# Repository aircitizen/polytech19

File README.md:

# polytech19

## Architecture
Le projet se décompose en trois parties
- Code du noeud LoRaWan
- PCB du noeud LoRaWan
- PCB de la gateway LoRaWan

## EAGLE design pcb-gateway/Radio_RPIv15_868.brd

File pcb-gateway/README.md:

# PCB gateway

Ici se situent les fichiers EAGLE du PCB de la gateway qui se connecte sur une Raspberry Pi B 3+.
Il y a également la BOM et des images.

Travail réalisé à partir du projet [https://github.com/will127534/LoRa-concentrator](https://github.com/will127534/LoRa-concentrator)

## RPi IO Mapping

| Function    | RPi Pin  | RPi IO Names                     |
| ----------- | -------- | -------------------------------- |
| SPI MOSI    | 19       | SPI-MOSI, GPIO10                 |
| SPI MISO    | 21       | SPI-MISO, GPIO9                  |
| SPI SCK     | 23       | SPI-SCLK, GPIO11                 |
| SPI CSN     | 24 OR 26 | SPI-CS0, GPIO8 OR SPI-CS1, GPIO7 |
| Reset       | 22       | GPIO25                           |
| GPS UART TX | 10       | UART0-RX, GPIO15                 |
| GPS UART RX | 8        | UART0-TX, GPIO14                 |
| GPS PPS     | 29       | GPIO5                            |

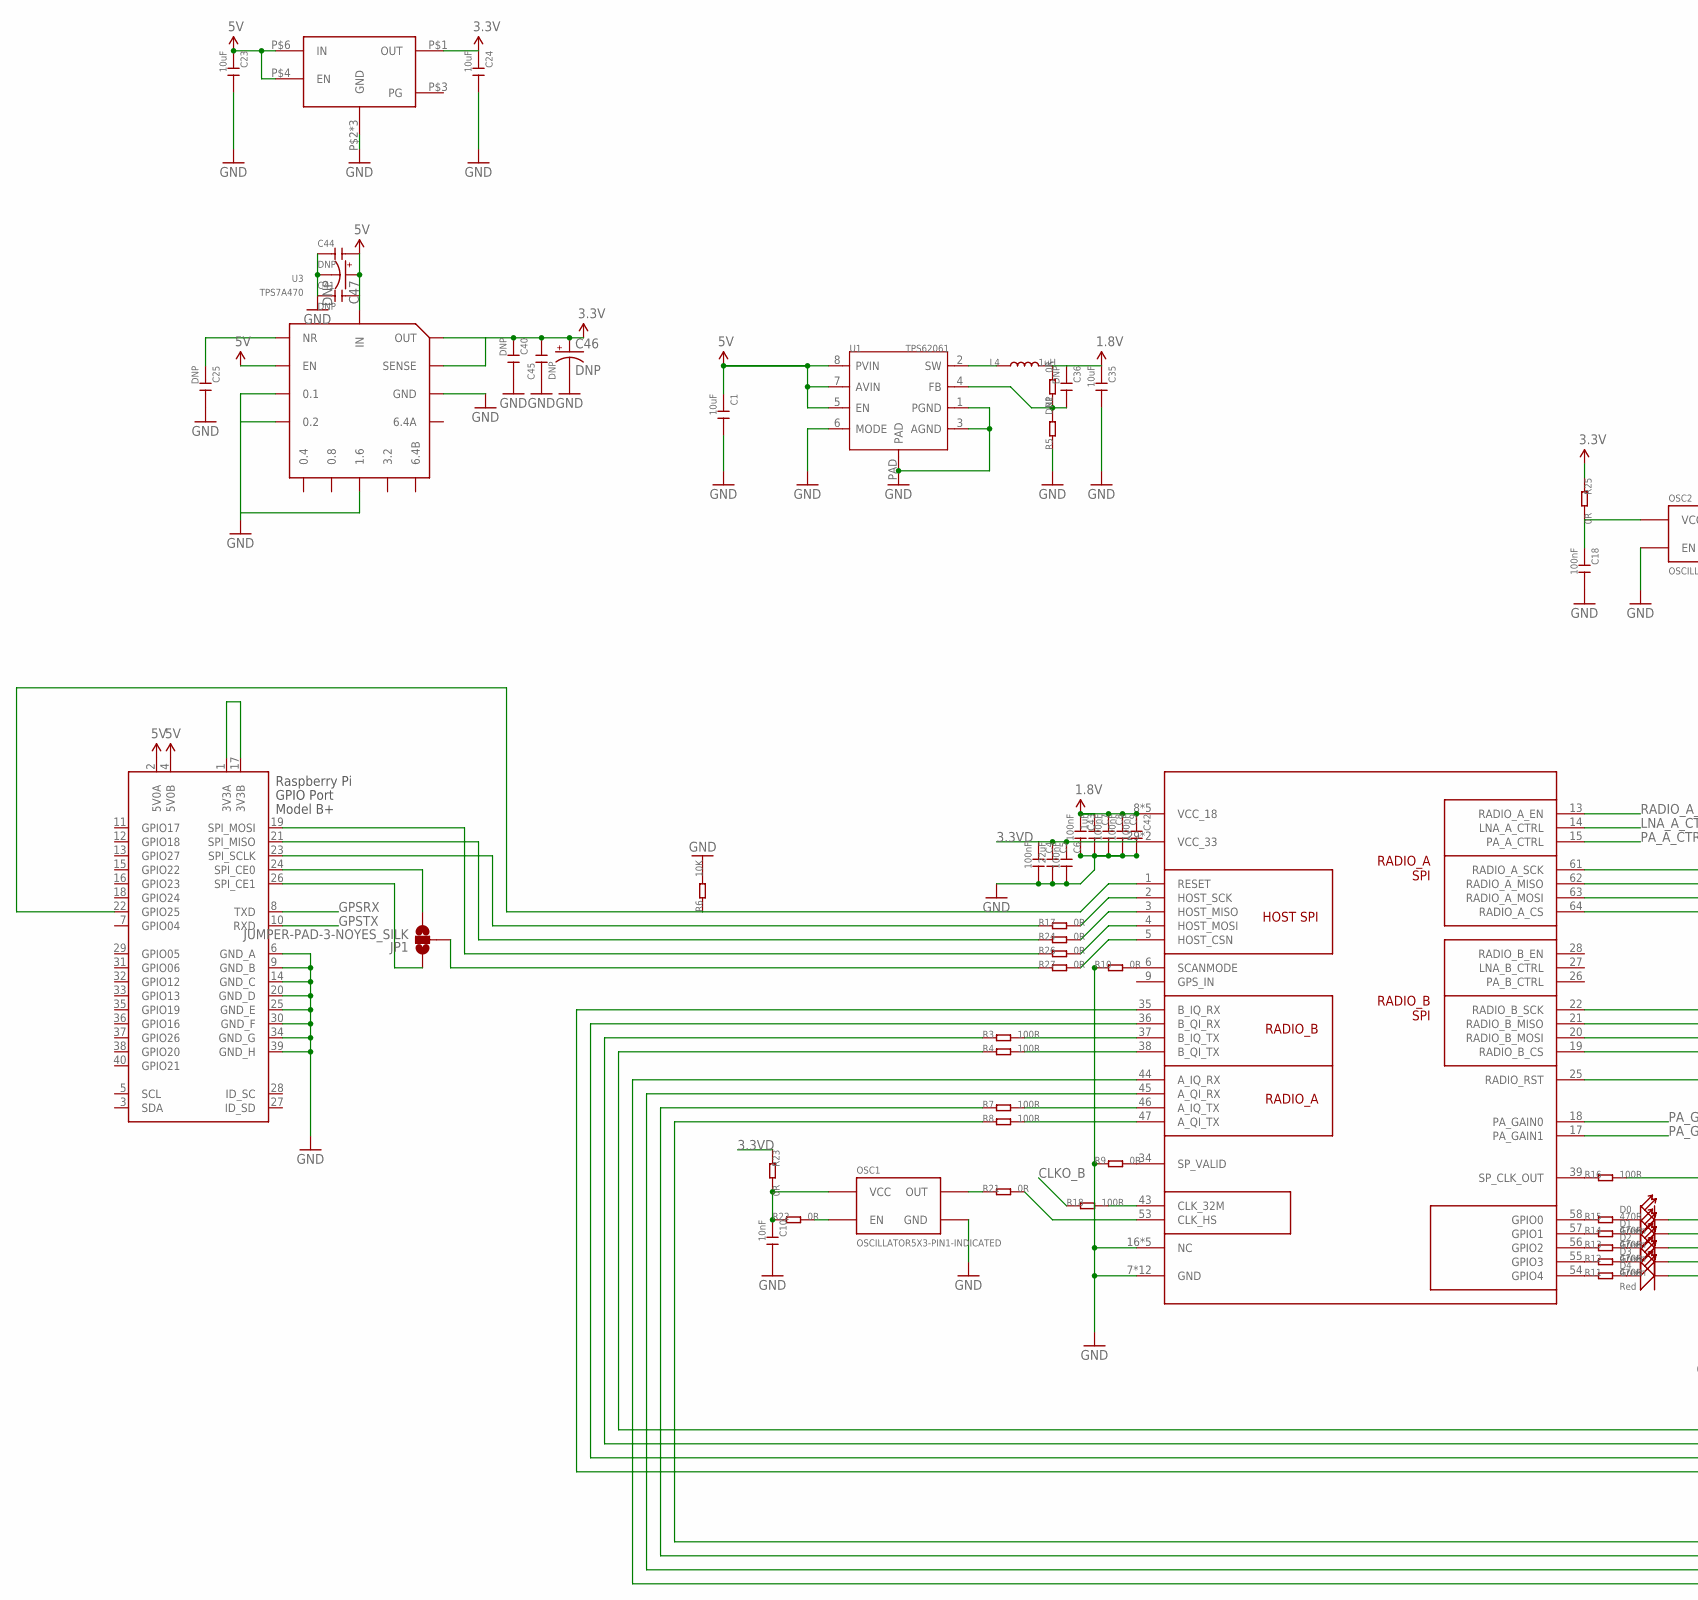
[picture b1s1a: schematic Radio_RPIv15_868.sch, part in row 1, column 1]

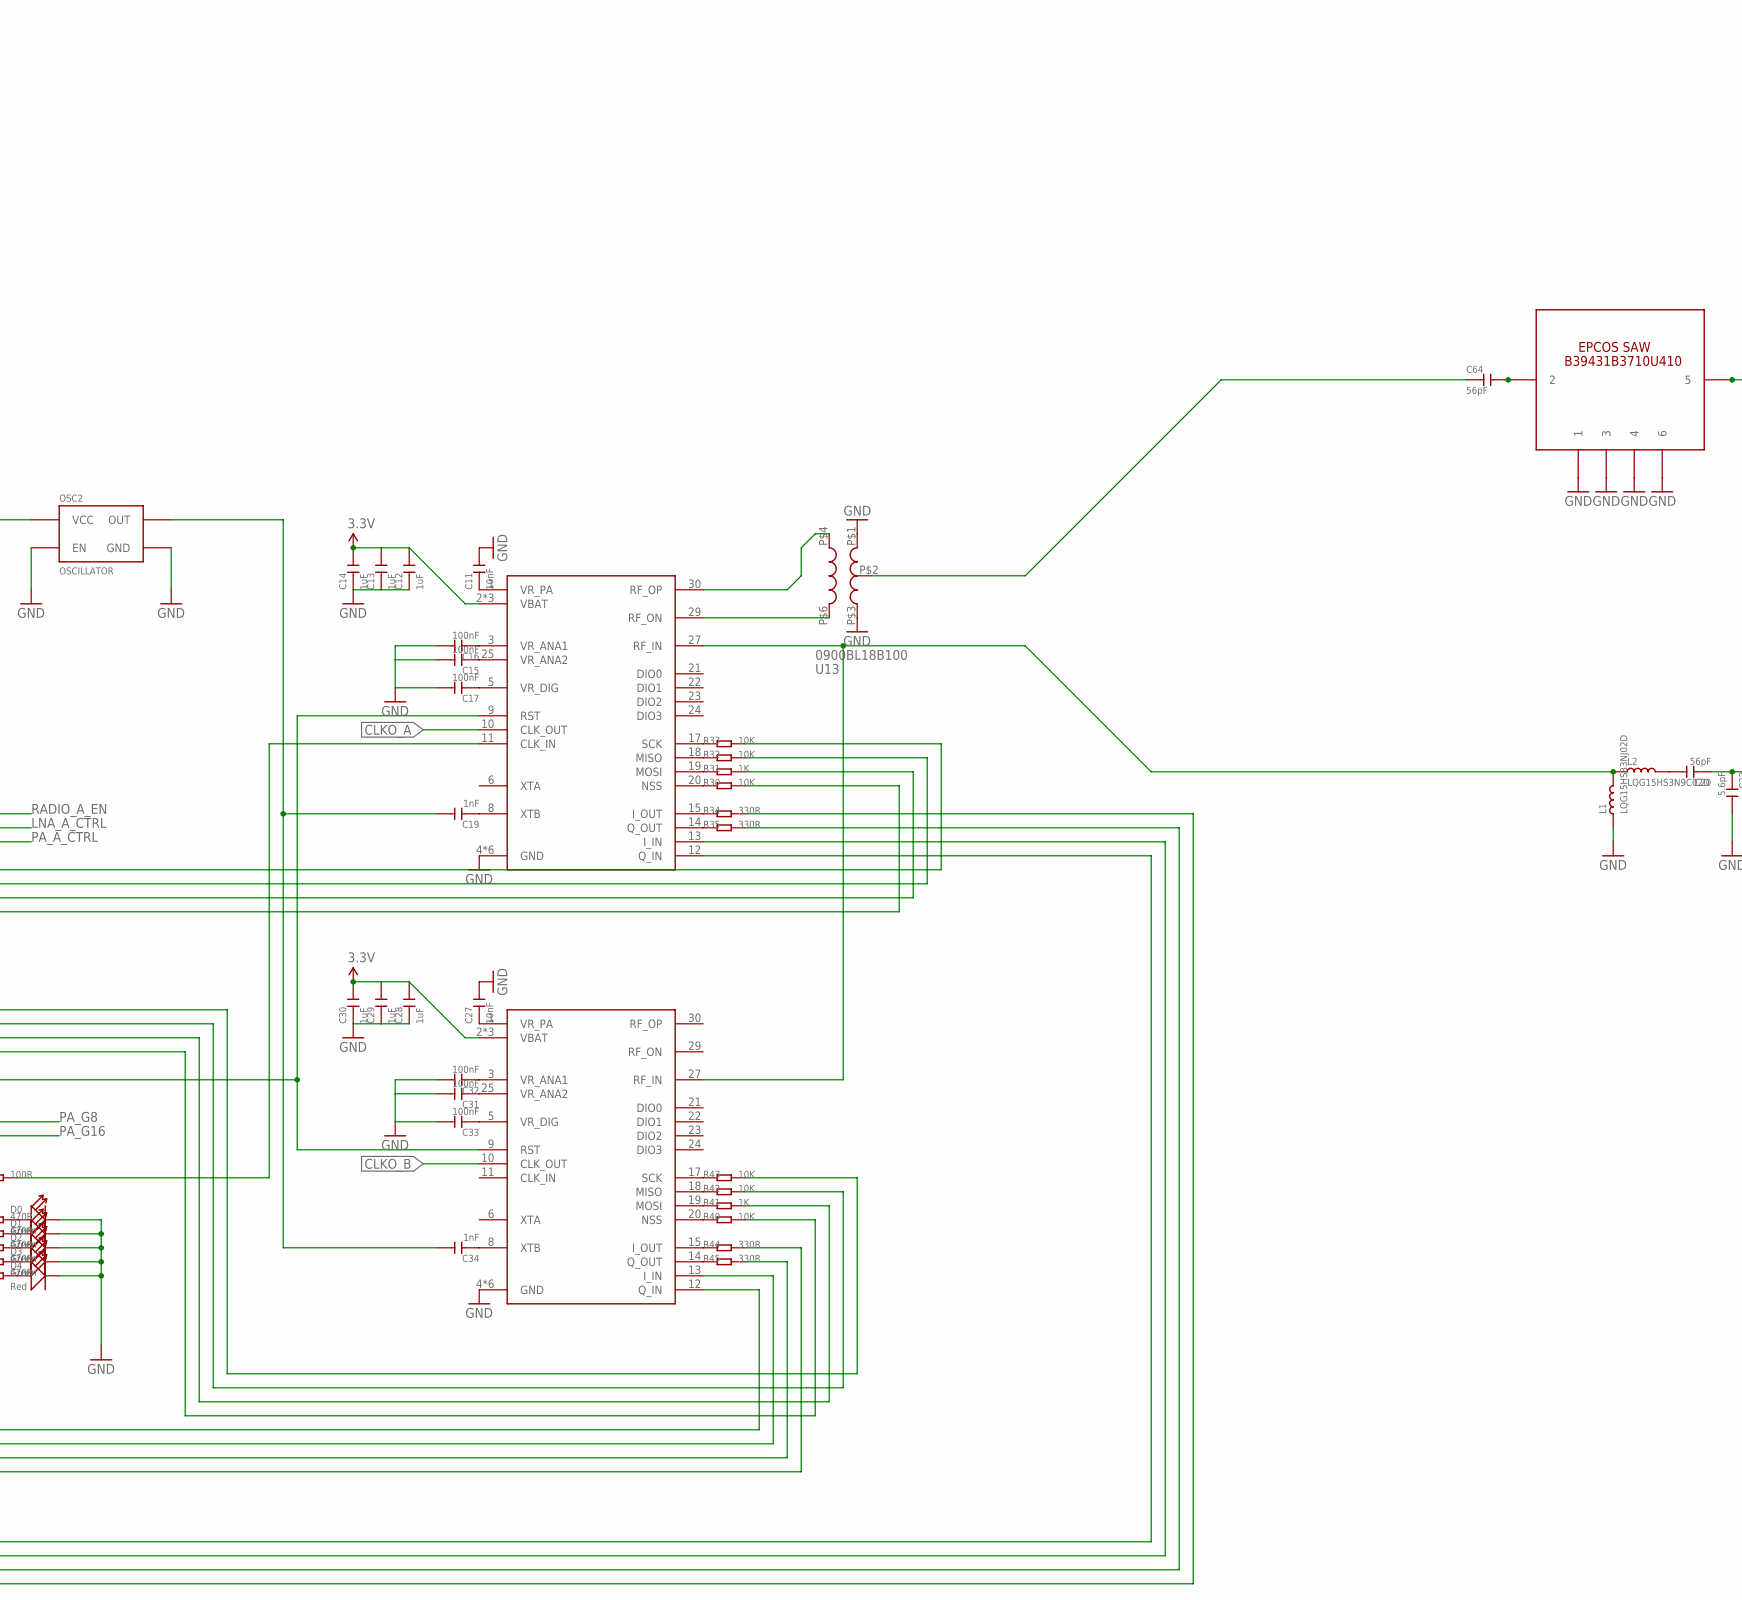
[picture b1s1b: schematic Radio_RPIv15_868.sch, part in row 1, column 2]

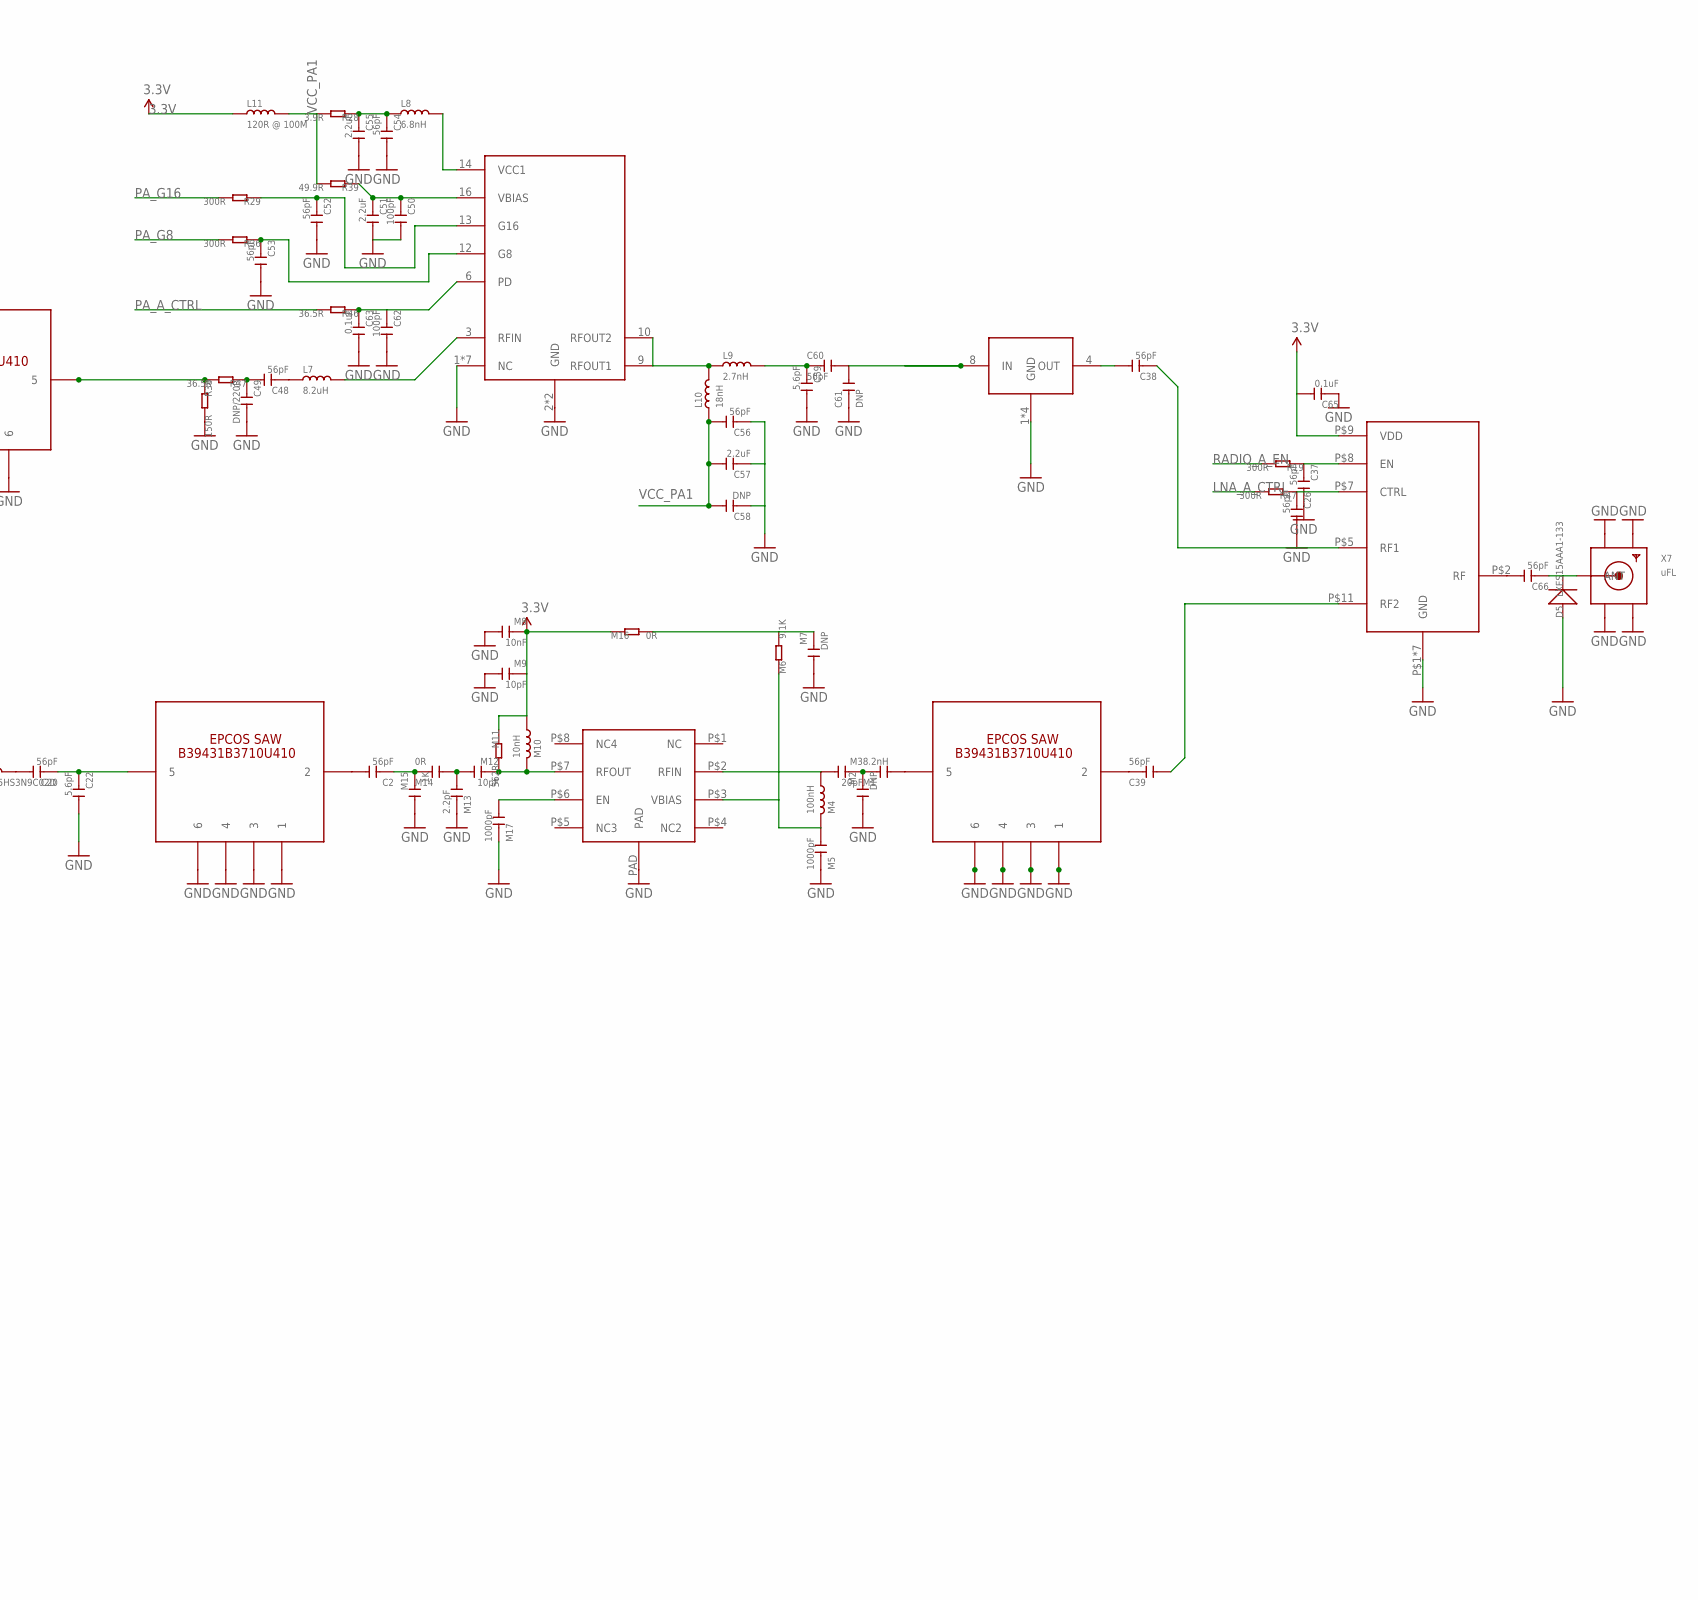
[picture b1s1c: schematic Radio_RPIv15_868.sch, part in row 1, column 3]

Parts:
C1, C23, C24, C35: 10uF; C0603@1
C2, C20, C26, C37, C38, C39, C48, C52, C53, C54, C56, C60, C64, C66: 56pF; C0402@1
C4, C6, C8, C9, C15, C16, C17, C18, C31, C32, C33, C42, C43: 100nF; C0402@1
C5: 22uF; C0402@1
C7, C12, C13, C14, C28, C29, C30: 1uF; C0402@1
C10, C11, C27: 10nF; C0402@1
C19, C34: 1nF; C0402@1
C22, C59: 5.6pF; C0402@1
C25, C36, C40, C41, C58, C61: DNP; C0402@1
C44, C45: DNP; C0805@1
C46, C47: DNP; EIA3216
C49: DNP/220R; C0402@1
C50, C62: 100pF; C0402@1
C51, C55, C57: 2.2uF; C0402@1
C63, C65: 0.1uF; C0402@1
D0, D1, D2, D3: Green; LED-0603
D4: Red; LED-0603
D5: LXES15AAA1-133; C0402
JP1: JUMPER-PAD-3-NOYES_SILK; PAD-JUMPER-3-NO_YES_SILK
L1: LQG15HS33NJ02D; L0402@1
L2: LQG15HS3N9C02D; L0402@1
L4: 1uH; 1616BZ
L7: 8.2uH; L0402@1
L8: 6.8nH; L0402@1
L9: 2.7nH; L0402@1
L10: 18nH; L0402@1
L11: 120R @ 100M; L0402@1
M1: 8.2nH; C0402@1
M2, M7: DNP; C0402@1
M3: 20pF; C0402@1
M4: 100nH; L0402@1
M5, M17: 1000pF; C0402@1
M6: 9.1K; R0402
M8: 10nF; C0402@1
M9, M12: 10pF; C0402@1
M10: 10nH; L0402@1
M11: 562R; R0402
M13: 2.2pF; C0402@1
M14: 0R; C0402@1
M15: 1K; C0402@1
M16: 0R; R0402
OSC1: OSCILLATOR5X3-PIN1-INDICATED; CRYSTAL-OSC-SMD-5X3
OSC2: OSCILLATOR; CRYSTAL-OSC-SMD-3.2X2.5
R1, R9, R10, R17, R21, R22, R23, R24, R25, R26, R27: 0R; R0402
R3, R4, R7, R8, R16, R18: 100R; R0402
R5: DNP; R0402
R6, R30, R32, R33, R40, R42, R43: 10K; R0402
R11, R12, R13, R14, R15: 470R; R0402
R19, R29, R36, R47: 300R; R0402
R28: 3.9R; R0402
R31, R41: 1K; R0402
R34, R35, R44, R45: 330R; R0402
R37, R46: 36.5R; R0402
R38: 150R; R0402
R39: 49.9R; R0402
U1: TPS62061; WSON
U3: TPS7A470; S-PVQFN-N20
U6: RFPA0133; QFN16-3X3MM
U13: 0900BL18B100; BALUN_1206
U$1: SX1301; QFN64G-0.5-9X9MM
U$2, U$3: SX1255; QFN32G-0.5-5X5MM
U$4, U$8: B39921B3728U410; EPCOS_SAW_FILTER
U$5: LP5912; WSON6
U$6: 0915LP15B026
U$7: RFSW1012; QFN12-2X2MM
U$9: EPCOS_SAW_FILTER
U$10: SKY67150_396LF; 8DFN
X1: RASPI_BOARD_B+#_H; RASPI_BOARD_B+HAT
X7: uFL; SMA_EDGELAUNCH_UFL

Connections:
1.8V: C7.1, C8.1, C9.1, C35.1, C36.1, C42.1, C43.1, L4.2, R1.2, U$1.8 (VCC_18), U$1.12 (VCC_18), U$1.23 (VCC_18), U$1.42 (VCC_18), U$1.60 (VCC_18)
3.3V: C12.2, C13.2, C14.2, C24.1, C28.2, C29.2, C30.2, C40.1, C45.2, C46.A (+), C65.2, L11.1, M8.1, M9.1, M10.2, M11.1, M16.1, R25.1, U3.1 (OUT), U3.3 (SENSE), U3.20 (OUT), U$2.2 (VBAT), U$2.16 (VBAT), U$2.32 (VBAT), U$3.2 (VBAT), U$3.16 (VBAT), U$3.32 (VBAT), U$5.P$1 (OUT), U$7.P$9 (VDD)
3.3VD: C4.1, C5.1, C6.1, R23.1, U$1.29 (VCC_33), U$1.52 (VCC_33)
5V: C1.1, C23.1, C41.2, C44.2, C47.A (+), U1.5 (EN), U1.7 (AVIN), U1.8 (PVIN), U3.13 (EN), U3.15 (IN), U3.16 (IN), U$5.P$4 (EN), U$5.P$6 (IN), X1.2 (5V0A), X1.4 (5V0B)
CLKO_A: U$2.10 (CLK_OUT)
CLKO_B: R18.1, U$3.10 (CLK_OUT)
CS: R27.2, U$1.5 (HOST_CSN)
FEWF: D4.+, R11.2
GND: C1.2, C4.2, C5.2, C6.2, C7.2, C8.2, C9.2, C10.2, C11.2, C12.1, C13.1, C14.1, C15.2, C16.2, C17.2, C18.2, C22.2, C23.2, C24.2, C25.2, C26.2, C27.2, C28.1, C29.1, C30.1, C31.2, C32.2, C33.2, C35.2, C37.2, C40.2, C41.1, C42.2, C43.2, C44.1, C45.1, C46.C (-), C47.C (-), C49.2, C50.2, C51.2, C52.2, C53.2, C54.2, C55.2, C56.1, C57.1, C58.1, C59.2, C61.1, C62.2, C63.2, C65.1, D0.-, D1.-, D2.-, D3.-, D4.-, D5.1 (+), L1.1, M2.2, M5.1, M7.2, M8.2, M9.2, M13.1, M15.2, M17.1, OSC1.2 (GND), OSC2.P$1 (EN), OSC2.P$2 (GND), R5.1, R6.2, R9.1, R10.1, R38.2, U1.1 (PGND), U1.3 (AGND), U1.6 (MODE), U1.PAD, U3.2 (GND), U3.7 (GND), U3.8 (1.6), U3.11 (0.2), U3.12 (0.1), U3.17 (GND), U3.18 (GND), U3.19 (GND), U3.EXP (GND), U6.1 (NC), U6.2 (GND), U6.4 (NC), U6.5 (NC), U6.7 (NC), U6.8 (NC), U6.11 (NC), U6.15 (NC), U6.EXT (GND), U13.P$1 (GND_1), U13.P$3 (GND_2), U$1.7 (GND), U$1.10 (GND), U$1.11 (GND), U$1.16 (NC), U$1.24 (GND), U$1.30 (GND), U$1.31 (GND), U$1.32 (NC), U$1.33 (NC), U$1.40 (GND), U$1.41 (GND), U$1.48 (NC), U$1.49 (NC), U$1.50 (GND), U$1.51 (GND), U$1.59 (GND), U$1.65 (GND), U$2.4 (GND), U$2.7 (GND), U$2.26 (GND), U$2.28 (GND), U$2.31 (GND), U$2.33 (GND), U$3.4 (GND), U$3.7 (GND), U$3.26 (GND), U$3.28 (GND), U$3.31 (GND), U$3.33 (GND), U$4.P$1 (1), U$4.P$3 (3), U$4.P$4 (4), U$4.P$6 (6), U$5.P$2 (GND), U$5.P$5 (GND), U$5.PAD (GND), U$6.1 (GND), U$6.3 (GND), U$6.5 (GND), U$6.7 (GND), U$7.P$1 (GND), U$7.P$3 (GND), U$7.P$4 (GND), U$7.P$6 (GND), U$7.P$10 (GND), U$7.P$12 (GND), U$7.PAD (GND), U$8.P$1 (1), U$8.P$3 (3), U$8.P$4 (4), U$8.P$6 (6), U$9.P$1 (1), U$9.P$3 (3), U$9.P$4 (4), U$9.P$6 (6), U$10.PAD, X1.6 (GND_A), X1.9 (GND_B), X1.14 (GND_C), X1.20 (GND_D), X1.25 (GND_E), X1.30 (GND_F), X1.34 (GND_G), X1.39 (GND_H), X7.GND@1 (GND1), X7.GND@2 (GND2), X7.GND@3 (GND3), X7.GND@4 (GND4)
GPSRX: X1.8 (TXD)
GPSTX: X1.10 (RXD)
LNA_A_CTRL: R47.2, U$1.14 (LNA_A_CTRL)
MISO: R24.1, X1.21 (SPI_MISO)
MOSI: R26.1, X1.19 (SPI_MOSI)
unnamed: R30.1, U$2.20 (NSS)
unnamed: R45.2, U$1.36 (B_QI_RX)
unnamed: R3.2, U$1.37 (B_IQ_TX)
unnamed: R4.2, U$1.38 (B_QI_TX)
unnamed: R34.2, U$1.44 (A_IQ_RX)
unnamed: R7.2, U$1.46 (A_IQ_TX)
unnamed: R8.2, U$1.47 (A_QI_TX)
unnamed: R35.2, U$1.45 (A_QI_RX)
unnamed: R9.2, U$1.34 (SP_VALID)
unnamed: R10.2, U$1.6 (SCANMODE)
unnamed: C20.2, L2.2
unnamed: R11.1, U$1.54 (GPIO4)
unnamed: R12.1, U$1.55 (GPIO3)
unnamed: R13.1, U$1.56 (GPIO2)
unnamed: R14.1, U$1.57 (GPIO1)
unnamed: R15.1, U$1.58 (GPIO0)
unnamed: C2.1, M14.1, M15.1
unnamed: D3.+, R12.2
unnamed: D1.+, R14.2
unnamed: D0.+, R15.2
unnamed: D2.+, R13.2
unnamed: R16.1, U$1.39 (SP_CLK_OUT)
unnamed: C38.2, U$6.4 (OUT)
unnamed: C64.1, U13.P$2 (UNBALANCE)
unnamed: L4.1, U1.2 (SW)
unnamed: C36.2, R1.1, R5.2, U1.4 (FB)
unnamed: JP1.3, X1.24 (SPI_CE0)
unnamed: C19.1, U$2.8 (XTB)
unnamed: R21.2, U$1.53 (CLK_HS)
unnamed: OSC1.3 (OUT), R21.1
unnamed: OSC1.1 (EN), R22.2
unnamed: C10.1, OSC1.4 (VCC), R22.1, R23.2
unnamed: C11.1, U$2.1 (VR_PA)
unnamed: C18.1, OSC2.P$4 (VCC), R25.2
unnamed: C19.2, C34.2, OSC2.P$3 (OUT)
unnamed: C15.1, U$2.25 (VR_ANA2)
unnamed: C16.1, U$2.3 (VR_ANA1)
unnamed: C17.1, U$2.5 (VR_DIG)
unnamed: C39.1, U$9.P$2 (2)
unnamed: R17.2, U$1.2 (HOST_SCK)
unnamed: C20.1, C22.1, U$4.P$5 (5)
unnamed: R18.2, U$1.43 (CLK_32M)
unnamed: C2.2, U$4.P$2 (2)
unnamed: R24.2, U$1.3 (HOST_MISO)
unnamed: L1.2, L2.1, U$2.27 (RF_IN), U$3.27 (RF_IN)
unnamed: R26.2, U$1.4 (HOST_MOSI)
unnamed: JP1.2, R27.1
unnamed: C25.1, U3.14 (NR)
unnamed: U13.P$4 (BALANCE_1), U$2.30 (RF_OP)
unnamed: U13.P$6 (BALANCE_2), U$2.29 (RF_ON)
unnamed: L7.2, U6.3 (RFIN)
unnamed: R34.1, U$2.15 (I_OUT)
unnamed: R35.1, U$2.14 (Q_OUT)
unnamed: C27.1, U$3.1 (VR_PA)
unnamed: C31.1, U$3.25 (VR_ANA2)
unnamed: C32.1, U$3.3 (VR_ANA1)
unnamed: C33.1, U$3.5 (VR_DIG)
unnamed: C34.1, U$3.8 (XTB)
unnamed: C48.1, L7.1
unnamed: C64.2, U$8.P$2 (2)
unnamed: C52.1, R29.1, U6.13 (G16)
unnamed: C53.1, R36.1, U6.12 (G8)
unnamed: L8.2, U6.14 (VCC1)
unnamed: C54.1, C55.1, L8.1, R28.1
unnamed: L9.1, L10.2, U6.9 (RFOUT1), U6.10 (RFOUT2)
unnamed: C59.1, C60.1, L9.2
unnamed: C60.2, C61.2, U$6.8 (IN)
unnamed: C48.2, C49.1, R37.1
unnamed: C62.1, C63.1, R46.1, U6.6 (PD)
unnamed: C38.1, U$7.P$5 (RF1)
unnamed: C66.2, U$7.P$2 (RF)
unnamed: R37.2, R38.1, U$8.P$5 (5)
unnamed: C26.1, R47.1, U$7.P$7 (CTRL)
unnamed: R44.1, U$3.15 (I_OUT)
unnamed: R45.1, U$3.14 (Q_OUT)
unnamed: R33.2, U$1.61 (RADIO_A_SCK)
unnamed: R32.2, U$1.62 (RADIO_A_MISO)
unnamed: R31.2, U$1.63 (RADIO_A_MOSI)
unnamed: R30.2, U$1.64 (RADIO_A_CS)
unnamed: R43.2, U$1.22 (RADIO_B_SCK)
unnamed: R42.2, U$1.21 (RADIO_B_MISO)
unnamed: R41.2, U$1.20 (RADIO_B_MOSI)
unnamed: R40.2, U$1.19 (RADIO_B_CS)
unnamed: U$1.25 (RADIO_RST), U$2.9 (RST), U$3.9 (RST)
unnamed: R16.2, U$2.11 (CLK_IN)
unnamed: R44.2, U$1.35 (B_IQ_RX)
unnamed: R7.1, U$2.13 (I_IN)
unnamed: R3.1, U$3.13 (I_IN)
unnamed: R4.1, U$3.12 (Q_IN)
unnamed: R8.1, U$2.12 (Q_IN)
unnamed: JP1.1, X1.26 (SPI_CE1)
unnamed: C66.1, D5.2 (-), X7.P (ANT)
unnamed: C39.2, U$7.P$11 (RF2)
unnamed: M1.2, U$9.P$5 (5)
unnamed: M1.1, M2.1, M3.1
unnamed: R31.1, U$2.19 (MOSI)
unnamed: R32.1, U$2.18 (MISO)
unnamed: R33.1, U$2.17 (SCK)
unnamed: R40.1, U$3.20 (NSS)
unnamed: R41.1, U$3.19 (MOSI)
unnamed: R42.1, U$3.18 (MISO)
unnamed: R43.1, U$3.17 (SCK)
unnamed: M6.2, M7.1, M16.2
unnamed: M10.1, M11.2, M12.1, U$10.P$7 (RFOUT)
unnamed: M12.2, M13.2, M14.2
unnamed: C37.1, R19.1, U$7.P$8 (EN)
unnamed: M17.2, U$10.P$6 (EN)
unnamed: M3.2, M4.2, U$10.P$2 (RFIN)
unnamed: M4.1, M5.2, M6.1, U$10.P$3 (VBIAS)
unnamed: X1.1 (3V3A), X1.17 (3V3B)
PA_A_CTRL: R46.2, U$1.15 (PA_A_CTRL)
PA_G8: R36.2, U$1.18 (PA_GAIN0)
PA_G16: R29.2, U$1.17 (PA_GAIN1)
RADIO_A_EN: R19.2, U$1.13 (RADIO_A_EN)
RST: R6.1, U$1.1 (RESET), X1.22 (GPIO25)
SCK: R17.1, X1.23 (SPI_SCLK)
VBIAS: C50.1, C51.1, R39.1, U6.16 (VBIAS)
VCC_PA1: C56.2, C57.2, C58.2, L10.1, L11.2, R28.2, R39.2

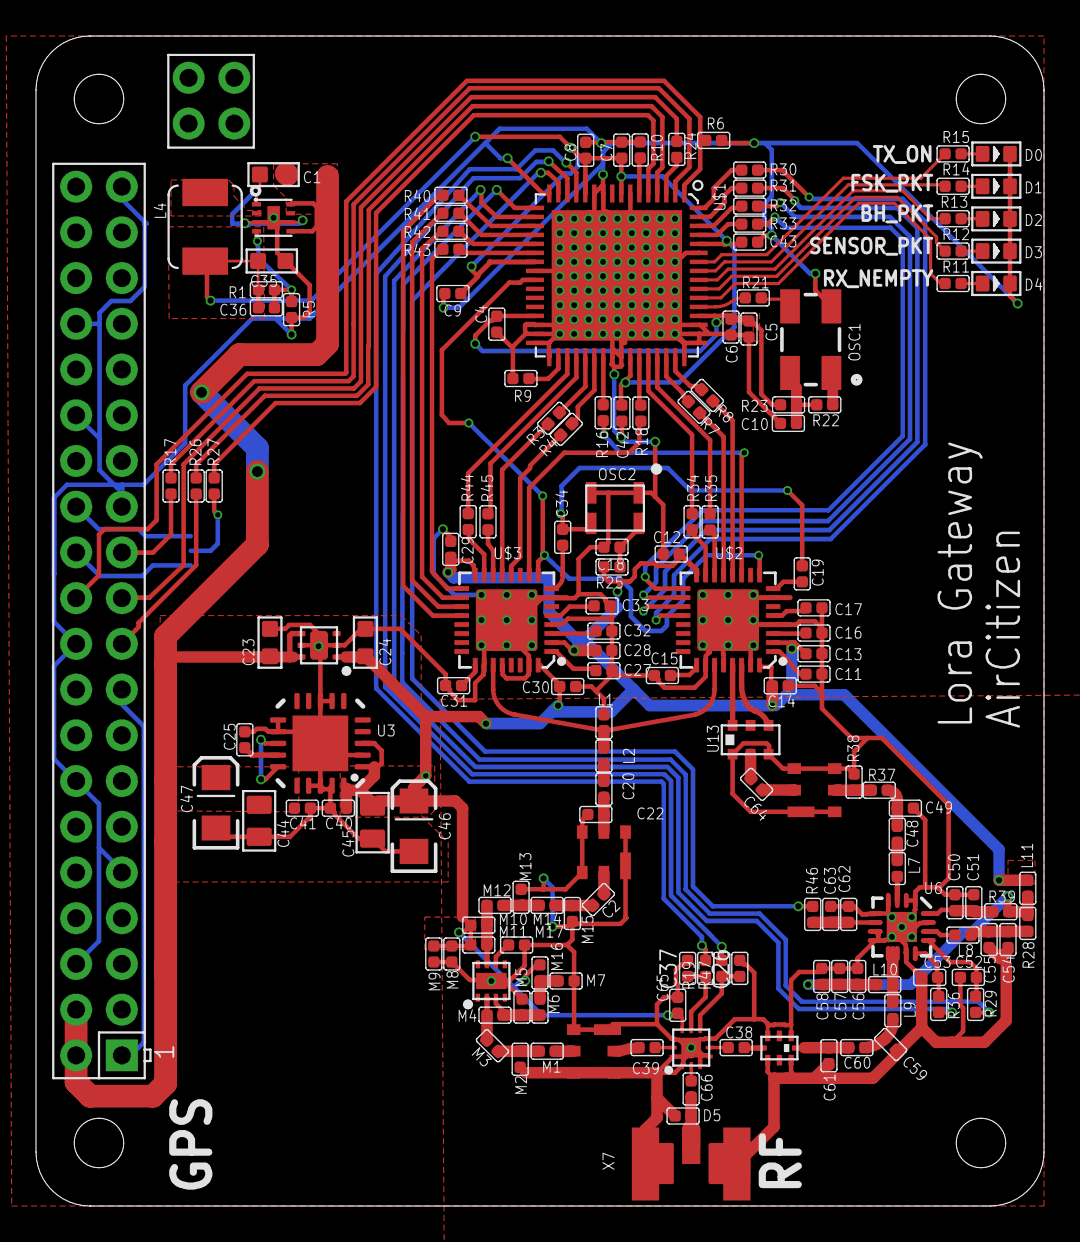
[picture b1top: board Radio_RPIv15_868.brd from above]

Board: 4 copper layers, 56.0 x 65.0 mm, 159 parts (1 on the bottom side), 129 nets.

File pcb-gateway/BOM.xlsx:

Qty | Value | Device | Package | Parts | Description
1.0 | LXES15AAA1-133 | D | C0402 | D5
1.0 | 0900BL18B100 | BALUN_1206 | BALUN_1206 | U13 | https://fr.farnell.com/johanson-technology/0900bl18b100e/bal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
1.0 | 0868LP15A020/0915LP15B026 | LowPassFilter | LowPassFilter | U$6 | https://fr.farnell.com/johanson-technology/0868lp15a020e/fil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
14.0 | 0R | R-0402 | R0402 | M16, R1, R9, R10, R17, R21, R22, R23, R24, R25, R26, R27, M14, L11 | https://fr.farnell.com/yageo/rc0402jr-070rl/res-couche-epais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
2.0 | 1000pF | CAP-0402 | C0402 | M5, M17 | https://fr.farnell.com/kemet/c0402s102k5ractu/cond-1000pf-50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
6.0 | 100R | R-0402 | R0402 | R3, R4, R7, R8, R16, R18 | https://fr.farnell.com/multicomp/mcwr04x1000ftl/resistance-t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
15.0 | 100nF | CAP-0402 | C0402 | C4, C6, C8, C9, C15, C16, C17, C18, C31, C32, C33, C42, C43, C63, C65
1.0 | 100nH | RF INDUCTOR | L0402 | M4
2.0 | 100pF | CAP-0402 | C0402 | C50, C62
7.0 | 10K | R-0402 | R0402 | R6, R20, R30, R32, R33, R40, R42, R43 | https://fr.farnell.com/vishay/crcw040210k0fked/res-couche-ep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
4.0 | 10nF | CAP-0402 | C0402 | C10, C11, C27, M8
1.0 | 10nH | RF INDUCTOR | L0402 | M10
2.0 | 10pF | CAP-0402 | C0402 | M9, M12
4.0 | 10uF | CAP-0603 | C0603 | C1, C23, C24, C35
1.0 | 150R | R-0402 | R0402 | R38 | https://fr.farnell.com/multicomp/mcwr04x1000ftl/resistance-t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
1.0 | 18nH | RF INDUCTOR | L0402 | L10
1.0 | 1K | CAP-0402 | C0402 | M15
2.0 | 1K | R-0402 | R0402 | R31, R41
2.0 | 1nF | CAP-0402 | C0402 | C19, C34
7.0 | 1uF | CAP-0402 | C0402 | C7, C12, C13, C14, C28, C29, C30
1.0 | 1uH | L'1616BZ' | 1616BZ | L4 | https://fr.farnell.com/vishay/ihlp1616bzer1r0m0h/inductance-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
1.0 | 2.2pF | CAP-0402 | C0402 | M13
3.0 | 2.2uF | CAP-0402 | C0402 | C51, C55, C57
1.0 | 2.7nH | RF INDUCTOR | L0402 | L9
1.0 | 20pF | CAP-0402 | C0402 | M3
1.0 | 22uF | CAP-0402 | C0402 | C5
1.0 | 3.9R | R-0402 | R0402 | R28 | https://fr.farnell.com/multicomp/mcwr04x3901ftl/resistance-t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
4.0 | 300R | R-0402 | R0402 | R19, R29, R36, R47
4.0 | 330R | R-0402 | R0402 | R34, R35, R44, R45
2.0 | 36.5R | R-0402 | R0402 | R37, R46
5.0 | 470R | R-0402 | R0402 | R11, R12, R13, R14, R15
1.0 | 49.9R | R-0402 | R0402 | R39
2.0 | 5.6pF | CAP-0402 | C0402 | C22, C59
1.0 | 562R | R-0402 | R0402 | M11
14.0 | 56pF | CAP-0402 | C0402 | C2, C20, C26, C37, C38, C39, C48, C52, C53, C54, C56, C60, C64, C66
1.0 | 6.8nH | RF INDUCTOR | L0402 | L8
1.0 | 8.2nH | CAP-0402 | C0402 | M1
1.0 | 8.2nH | RF INDUCTOR | L0402 | L7
1.0 | 9.1K | R-0402 | R0402 | M6
3.0 | B39921B3728U410/B39871B3717U410 | EPCOS_SAW_FILTER | EPCOS_SAW_FILTER | U$4, U$8, U$9 | https://fr.farnell.com/epcos/b39871b3715u410/saw-filter-rf-8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
4.0 | Green | LED-0603 | LED-0603 | D0, D1, D2, D3 | https://fr.farnell.com/rohm/sml-d12p8wt86c/led-aec-q101-vert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
1.0 | LP5912 | LP5912 | WSON6 | U$5 | https://fr.farnell.com/texas-instruments/lp5912-3-3drvt/reg-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
1.0 | LQG15HS33NJ02D | RF INDUCTOR | L0402 | L1 | https://fr.farnell.com/murata/lqg15hn33nj02d/inductance-33nh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
1.0 | LQG15HS3N9C02D | RF INDUCTOR | L0402 | L2 | https://fr.farnell.com/murata/lqg15hs3n9s02d/inductance-3-9n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
1.0 | 32Mhz TXCO | OSCILLATOR | CRYSTAL-OSC-SMD-3.2X2.5 | OSC2
1.0 | 133Mhz | OSCILLATOR5X3-PIN1-INDICATED | CRYSTAL-OSC-SMD-5X3 | OSC1 | https://www.alibaba.com/product-detail/WTL-High-Frequency-3-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
1.0 | RASPI_BOARD_B+#_H | RASPI_BOARD_B+#_H | RASPI_BOARD_B+HAT | X1
1.0 | RFPA0133 | RFPA0133 | QFN16-3X3MM | U6 | https://fr.farnell.com/rfmd/rfpa0133/amp-rf-380-960mhz-3-5v-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
1.0 | RFSW1012 | RFSW1012 | QFN12-2X2MM | U$7 | https://www.mouser.fr/ProductDetail/Qorvo/RFSW1012TR7?qs=sGA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
1.0 | Red | LED-0603 | LED-0603 | D4 | https://fr.farnell.com/rohm/sml-d12u8wt86c/led-aec-q101-roug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
1.0 | SKY67150_396LF | SKY67150_396LF | 8DFN | U$10 | https://www.digikey.fr/product-detail/fr/skyworks-solutions-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
2.0 | SX1255 | SX1255 | QFN32G-0.5-5X5MM | U$2, U$3 | https://www.mouser.fr/ProductDetail/Semtech/SX1255-55SKA433?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
1.0 | SX1301 | SX1301 | QFN64G-0.5-9X9MM | U$1 | https://www.mouser.fr/ProductDetail/Semtech/SX1301IMLTRC?qs=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
1.0 | TPS62061 | PMIC-ETA3410D2I-T(DFN8-2X2)WSON | WSON | U1 | https://www.mouser.fr/ProductDetail/Texas-Instruments/TPS620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
1.0 | SMA | SMACONNECTOR_EDGE_UFL | SMA_EDGELAUNCH_UFL | X7 | https://fr.farnell.com/multicomp/19-70-tgg/jack-sma/dp/1342651

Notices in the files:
parts and their libraries:
SparkFun-FreqCtrl: Licensing: Creative Commons ShareAlike 4.0 International - https://creativecommons.org/licenses/by-sa/4.0
microbuilder: This work is placed in the public domain, and may be freely used for commercial and non-commercial work with the following conditions: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
